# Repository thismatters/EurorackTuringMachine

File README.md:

# Turing Machine

The Turing Machine is a hugely popular module which produces random sequences of configurable length which can be held constant, or allowed to change slowly over time. Think of it like a sample-hold for sequences.

The circuit here is based on the [Music Thing Modular Turing Machine](https://github.com/TomWhitwell/TuringMachine) with some minor tweaks. The changes I've made are thus:
* Added polarity protection so that a backward power header doesn't fry anything (twin series schotty diodes: BAT54SL),
* Full surface mount design on a single PCB,
* Simpler input power filtering,
* Expanded length choices to include 7, 9, 11, and 13 (in addition to the default 2, 3, 4, 5, 6, 8, 12, and 16).
* Schmitt trigger with hysteresis on clock input to handle input signals which aren't perfectly smooth (alleviating the tendancy of the Music Thing Modular circuit to double-clock)

This module should be a drop-in replacement for the Musing Thing Modular version with the same width and same basic panel layout. I've altered it somewhat to fit with the aesthetic and practices of my DIY build, however the pinouts for expansion modules adhere exactly to the original. This repo inherits the same license as the original Turing Machine: [CC-BY-SA](https://creativecommons.org/licenses/by-sa/3.0/)

The KiCAD project here uses the library/footprints [found in my companion repo](https://github.com/thismatters/EurorackKiCAD).

Note resistors R1 and R2 have been removed. You will not find them in the schematic or BOM.

## Width

10hp

## Inputs

Jacks:
- Clock (required input) -- Max clock rate: 1300Hz; higher frequencies will cause bit smearing.
- CV for setting "Change" rate

Knobs:
- Change rate
- Sequence length (12 position switch)
- Scale

Write switch for setting the current bit high or low.

## Outputs

Jacks:
- CV output of of sequence
- Whitenoise
- Pulse whenever the current bit is high

LEDs:
- 8x for the current binary representation of the output tone
- 1x for the pulse
- 1x for the clock input

## Vendors

There are part numbers in the [BOM](turing-machine.csv) for many of the parts (not for basic passives though) at the following vendors:

* [Mouser](https://www.mouser.com): Needs no introduction. Get your ICs from here (or [digikey](https://www.digikey.com)).
* [Tayda Electronics](https://www.taydaelectronics.com/): Good supplier for passive components; audio jacks, and potentiometers. Their audio jacks are slightly smaller than the thonkiconn from thonk.
* [Love My Switches](https://lovemyswitches.com/): Has [really good knobs](https://lovemyswitches.com/anodized-aluminum-knob-the-lo-fi-1-4-smooth-shaft-12-5mm-od/) to go on those potentiometers!
* [OSHPark](https://oshpark.com/): Fast and (relatively) cheap PCB manufacturer. ~[V1 board works great!](https://oshpark.com/shared_projects/wF94N3Eb)~ There is a problem with the randomness and change circuitry. Needs a new version.

## Changelog

### V1

* [x] Fixed pinout for DAC0800 which is different for SOIC than PDIP
* [x] Write switch rotated 180deg
* [x] Filters between shift registers removed (max clock rate confirmed at around 1330Hz (E6))
* [x] Schmitt trigger supplements op-amp in gate input stage
* [x] Flipped trimmer and added hole to front panel so that trimming can happen _in-situ_, added note to PCB about how the trimmer should be oriented.

### V1a

* [x] Corrected C12 to have value of 1nF
* [x] Added test points for:
  * LOOP_CTRL'
  * RAND'
* [x] Investigated noise interference
  * When several LEDs are lit the noise level drops dramatically
  * clipping the LEDS from the prototype PCB alleviated the problem.
  * It seems produent to run the LEDS from the buffer outputs (which drive the expanders), and to drive the buffers from an isolated power circuit.
* [x] tested the V1 circuit driving LEDs from expander to see if secondary power circuit is necessary
  * it is. Driving the LEDs via the buffer still brings the +12V rail from 11.45V to 11.15V
* [x] Tested if ferrite bead in place of 10ohm resistor for power conditioning corrects noise interference issue (seems to work fine)
* [x] Updated power circuit to use ferrite bead (81-BLM21SP700BH1D) instead of resistor to more closely match original design

#### V1 -> V1a refit
* Change capacitor C12 value to 1nF.
* Use ferrite bead in place of resistors R1 and R2. A suitable part with an matching footprint is available from Mouser.com: part number 81-BLM21SP700BH1D.

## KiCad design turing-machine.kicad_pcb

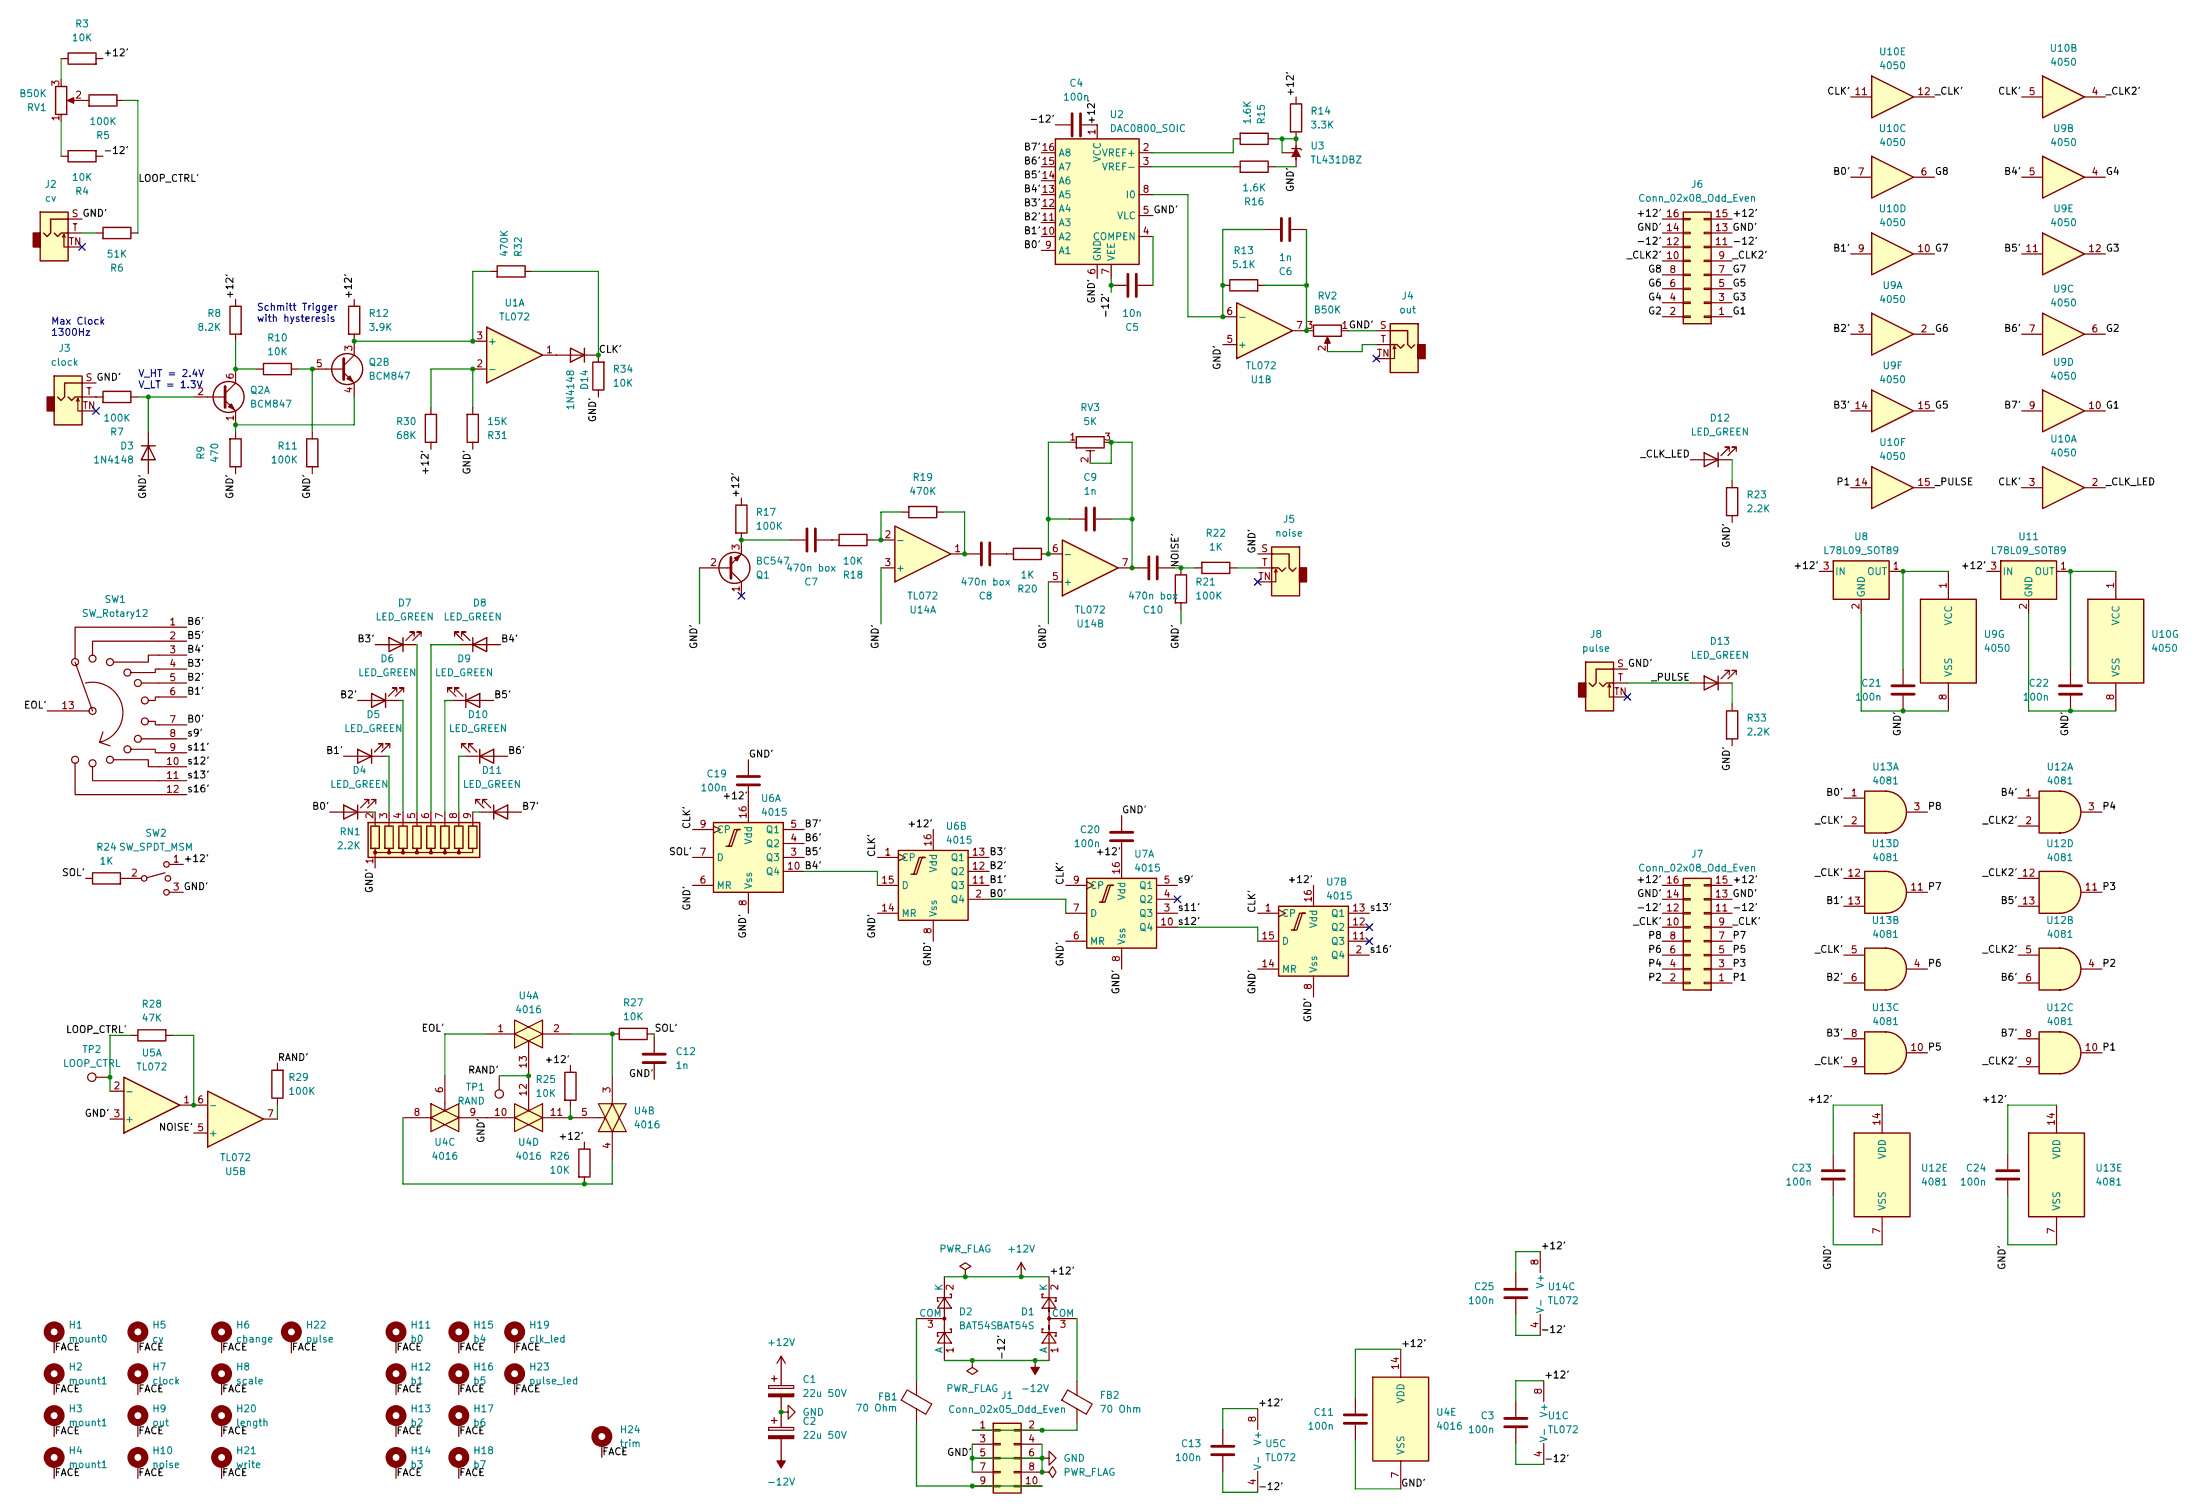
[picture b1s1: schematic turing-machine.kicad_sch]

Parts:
C1, C2: 22u 50V; CP_Radial_D5.0mm_P2.50mm
C3, C4, C11, C13, C19, C20, C21, C22, C23, C24, C25: 100n; C_0805_2012Metric
C5: 10n; C_0805_2012Metric
C6, C9, C12: 1n; C_0805_2012Metric
C7, C8, C10: 470n box; C_Rect_L7.2mm_W4.5mm_P5.00mm_FKS2_FKP2_MKS2_MKP2
D1, D2: BAT54S; SOT-23; PartNum 863-BAT54SLT1G
D3, D14: 1N4148; D_SOD-323_HandSoldering
D4, D5, D6, D7, D8, D9, D10, D11, D12, D13: LED_GREEN; LED_D3.0mm
FB1, FB2: 70 Ohm; L_0805_2012Metric; PartNum 81-BLM21SP700BH1D
H1: mount0; Mech-MountingHole
H2, H3, H4: mount1; Mech-MountingHole
H5: cv; Mech-AudioJack-Hole-Input-CV
H6: change; Mech-Potentiometer-Hole_level_180deg
H7: clock; Mech-AudioJack-Hole-Input-Clock
H8: scale; Mech-Potentiometer-Hole_level
H9: out; Mech-AudioJack-Hole-Output-CV
H10: noise; Mech-AudioJack-Hole-Output
H11: b0; Mech-LED-Hole-3mm
H12: b1; Mech-LED-Hole-3mm
H13: b2; Mech-LED-Hole-3mm
H14: b3; Mech-LED-Hole-3mm
H15: b4; Mech-LED-Hole-3mm
H16: b5; Mech-LED-Hole-3mm
H17: b6; Mech-LED-Hole-3mm
H18: b7; Mech-LED-Hole-3mm
H19: clk_led; Mech-LED-Hole-3mm
H20: length; Mech-MRK-Hole
H21: write; Mech-1M_Switch-Hole
H22: pulse; Mech-AudioJack-Hole-Output-Gate
H23: pulse_led; Mech-LED-Hole-3mm
H24: trim; Mech-LED-Hole-3mm
J1: Conn_02x05_Odd_Even; PinHeader_2x05_P2.54mm_Vertical; PartNum A-2939
J2: cv; AudioJack2_Tayda_A-2566; PartNum A-2566
J3: clock; AudioJack2_Tayda_A-2566; PartNum A-2566
J4: out; AudioJack2_Tayda_A-2566; PartNum A-2566
J5: noise; AudioJack2_Tayda_A-2566; PartNum A-2566
J6, J7: Conn_02x08_Odd_Even; PinHeader_2x08_P2.54mm_Vertical; PartNum A-2956
J8: pulse; AudioJack2_Tayda_A-2566; PartNum A-2566
Q1: BC547; TO-92_Inline_Wide; PartNum 637-BC547C
Q2: BCM847; TSOP-6_1.65x3.05mm_P0.95mm; PartNum 771-BCM847DS135
R3, R4, R10, R18, R25, R26, R27, R34: 10K; R_0805_2012Metric
R5, R7, R11, R17, R21, R29: 100K; R_0805_2012Metric
R6: 51K; R_0805_2012Metric
R8: 8.2K; R_0805_2012Metric
R9: 470; R_0805_2012Metric
R12: 3.9K; R_0805_2012Metric
R13: 5.1K; R_0805_2012Metric
R14: 3.3K; R_0805_2012Metric
R15, R16: 1.6K; R_0805_2012Metric
R19, R32: 470K; R_0805_2012Metric
R20, R22, R24: 1K; R_0805_2012Metric
R23, R33: 2.2K; R_0805_2012Metric
R28: 47K; R_0805_2012Metric
R30: 68K; R_0805_2012Metric
R31: 15K; R_0805_2012Metric
RN1: 2.2K; R_Array_SIP9; PartNum 652-4609X-1LF-2.2K
RV1, RV2: B50K; Potentiometer_RV16AF-41-15R1
RV3: 5K; Potentiometer_Bourns_3296W_Vertical
SW1: SW_Rotary12; Switch_Rotary_NKK_MRK_112; PartNum 633-MRK112-BA
SW2: SW_SPDT_MSM; Switch_SPDT_1M_Solder_Lug; PartNum A-6099
TP1: RAND; TestPoint_Plated_Hole_D2.0mm
TP2: LOOP_CTRL; TestPoint_Plated_Hole_D2.0mm
U1, U5, U14: TL072; SOIC-8_3.9x4.9mm_P1.27mm; PartNum 595-TL072CDR
U2: DAC0800_SOIC; SOIC-16_3.9x9.9mm_P1.27mm; PartNum 926-DAC0800LCMX/NOPB
U3: TL431DBZ; SOT-23; PartNum 595-TL431BCDBZTG4
U4: 4016; TSSOP-14_4.4x5mm_P0.65mm; PartNum 595-CD4016BPWR
U6, U7: 4015; TSSOP-16_4.4x5mm_P0.65mm; PartNum 595-CD4015BPWR
U8, U11: L78L09_SOT89; SOT-89-3; PartNum 511-L78L09ACU
U9, U10: 4050; TSSOP-16_4.4x5mm_P0.65mm; PartNum 595-CD4050BPWR
U12, U13: 4081; TSSOP-14_4.4x5mm_P0.65mm; PartNum 595-CD4081BPWR

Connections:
+12V: C1.1, C3.1, C4.2, C11.1, C13.1, C19.2, C20.2, C23.1, C24.1, C25.1, D1.2 (K), D2.2 (K), J6.15, J6.16, J7.15, J7.16, R3.2, R8.1, R12.1, R14.1, R17.1, R25.1, R26.1, R30.2, SW2.1, U1.8 (V+), U2.1 (VCC), U4.14 (VDD), U5.8 (V+), U6.16 (Vdd), U7.16 (Vdd), U8.3 (IN), U11.3 (IN), U12.14 (VDD), U13.14 (VDD), U14.8 (V+)
-12V: C2.2, C3.2, C4.1, C5.1, C13.2, C25.2, D1.1 (A), D2.1 (A), J6.11, J6.12, J7.11, J7.12, R4.2, U1.4 (V-), U2.7 (VEE), U5.4 (V-), U14.4 (V-)
/B0': D4.2 (A), SW1.7, U2.9 (A1), U6.2 (Q4), U7.7 (D), U10.7, U13.1
/B1': D5.2 (A), SW1.6, U2.10 (A2), U6.11 (Q3), U10.9, U13.13
/B2': D6.2 (A), SW1.5, U2.11 (A3), U6.12 (Q2), U9.3, U13.6
/B3': D7.2 (A), SW1.4, U2.12 (A4), U6.13 (Q1), U9.14, U13.8
/B4': D8.2 (A), SW1.3, U2.13 (A5), U6.10 (Q4), U6.15 (D), U9.5, U12.1
/B5': D9.2 (A), SW1.2, U2.14 (A6), U6.3 (Q3), U9.11, U12.13
/B6': D10.2 (A), SW1.1, U2.15 (A7), U6.4 (Q2), U9.7, U12.6
/B7': D11.2 (A), U2.16 (A8), U6.5 (Q1), U9.9, U12.8
/CLK': D14.1 (K), R32.1, R34.2, U6.1 (CP), U6.9 (CP), U7.1 (CP), U7.9 (CP), U10.3, U10.5, U10.11
/EOL': SW1.13, U4.1, U4.6
/FACE: H1.1, H2.1, H3.1, H4.1, H5.1, H6.1, H7.1, H8.1, H9.1, H10.1, H11.1, H12.1, H13.1, H14.1, H15.1, H16.1, H17.1, H18.1, H19.1, H20.1, H21.1, H22.1, H23.1, H24.1
/G1: J6.1, U9.10
/G2: J6.2, U9.6
/G3: J6.3, U9.12
/G4: J6.4, U9.4
/G5: J6.5, U9.15
/G6: J6.6, U9.2
/G7: J6.7, U10.10
/G8: J6.8, U10.6
/LOOP_CTRL': R5.1, R6.1, R28.1, TP2.1, U5.2 (-)
/NOISE': C10.2, R21.1, R22.2, U5.5 (+)
/P1: J7.1, U10.14, U12.10
/P2: J7.2, U12.4
/P3: J7.3, U12.11
/P4: J7.4, U12.3
/P5: J7.5, U13.10
/P6: J7.6, U13.4
/P7: J7.7, U13.11
/P8: J7.8, U13.3
/RAND': R29.2, TP1.1, U4.12, U4.13
/SOL': C12.1, R24.1, R27.2, U6.7 (D)
/_CLK2': J6.9, J6.10, U10.4, U12.2, U12.5, U12.9, U12.12
/_CLK': J7.9, J7.10, U10.12, U13.2, U13.5, U13.9, U13.12
/_CLK_LED: D12.2 (A), U10.2
/_PULSE: D13.2 (A), J8.T, U10.15
/s9': SW1.8, U7.5 (Q1)
/s11': SW1.9, U7.3 (Q3)
/s12': SW1.10, U7.10 (Q4), U7.15 (D)
/s13': SW1.11, U7.13 (Q1)
/s16': SW1.12, U7.2 (Q4)
GND: C1.2, C2.1, C11.2, C12.2, C19.1, C20.1, C21.2, C22.2, C23.2, C24.2, D3.2 (A), J1.3, J1.4, J1.5, J1.6, J1.7, J1.8, J2.S, J3.S, J4.S, J5.S, J6.13, J6.14, J7.13, J7.14, J8.S, Q1.2 (B), R9.1, R11.2, R16.1, R21.2, R23.2, R31.1, R33.2, R34.1, RN1.1 (common), RV2.1, SW2.3, U1.5 (+), U2.5 (VLC), U2.6 (GND), U3.3 (A), U4.7 (VSS), U4.9, U4.10, U5.3 (+), U6.6 (MR), U6.8 (Vss), U6.14 (MR), U7.6 (MR), U7.8 (Vss), U7.14 (MR), U8.2 (GND), U9.8 (VSS), U10.8 (VSS), U11.2 (GND), U12.7 (VSS), U13.7 (VSS), U14.3 (+), U14.5 (+)
unnamed: C6.2, R13.2, RV2.3, U1.7
unnamed: C7.2, R18.2
unnamed: C8.1, R19.1, U14.1
unnamed: C8.2, R20.2
unnamed: C9.2, C10.1, RV3.2, RV3.3, U14.7
unnamed: D1.3 (COM), FB2.1
unnamed: D2.3 (COM), FB1.1
unnamed: D3.1 (K), Q2.2 (B1), R7.1
unnamed: D4.1 (K), RN1.2 (R1)
unnamed: D5.1 (K), RN1.3 (R2)
unnamed: D6.1 (K), RN1.4 (R3)
unnamed: D7.1 (K), RN1.5 (R4)
unnamed: D8.1 (K), RN1.6 (R5)
unnamed: D9.1 (K), RN1.7 (R6)
unnamed: D10.1 (K), RN1.8 (R7)
unnamed: D11.1 (K), RN1.9 (R8)
unnamed: D12.1 (K), R23.1
unnamed: D13.1 (K), R33.1
unnamed: D14.2 (A), U1.1
unnamed: FB2.2, J1.1, J1.2
unnamed: FB1.2, J1.9, J1.10
unnamed: J2.T, R6.2
unnamed: J3.T, R7.2
unnamed: J4.T, RV2.2
unnamed: J5.T, R22.1
unnamed: C7.1, Q1.3 (E), R17.2
unnamed: Q2.6 (C1), R8.2, R10.1
unnamed: Q2.1 (E1), Q2.4 (E2), R9.2
unnamed: Q2.5 (B2), R10.2, R11.1
unnamed: Q2.3 (C2), R12.2, R32.2, U1.3 (+)
unnamed: R3.1, RV1.3
unnamed: R4.1, RV1.1
unnamed: R5.2, RV1.2
unnamed: R24.2, SW2.2
unnamed: R25.2, U4.5, U4.11
unnamed: R26.2, U4.4, U4.8
unnamed: R27.1, U4.2, U4.3
unnamed: R29.1, U5.7
unnamed: R30.1, R31.2, U1.2 (-)
unnamed: C6.1, R13.1, U1.6 (-), U2.8 (I0)
unnamed: C5.2, U2.4 (COMPEN)
unnamed: R15.2, U2.2 (VREF+)
unnamed: R16.2, U2.3 (VREF-)
unnamed: R14.2, R15.1, U3.1 (K), U3.2 (REF)
unnamed: R28.2, U5.1, U5.6 (-)
unnamed: C21.1, U8.1 (OUT), U9.1 (VCC)
unnamed: C22.1, U10.1 (VCC), U11.1 (OUT)
unnamed: R18.1, R19.2, U14.2 (-)
unnamed: C9.1, R20.1, RV3.1, U14.6 (-)

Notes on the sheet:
Schmitt Trigger with hysteresis
Max Clock 1300Hz
V_HT = 2.4V V_LT = 1.3V

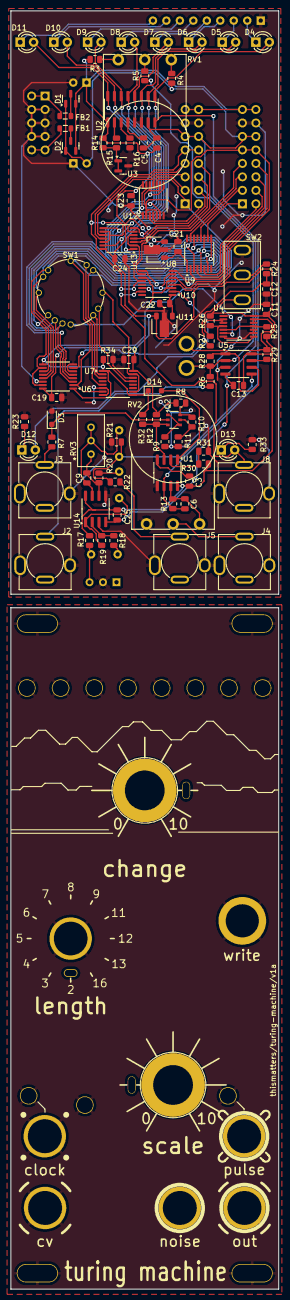
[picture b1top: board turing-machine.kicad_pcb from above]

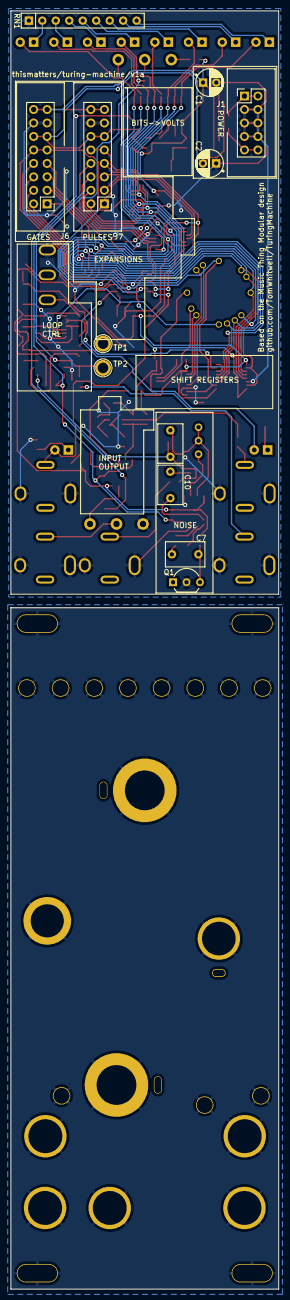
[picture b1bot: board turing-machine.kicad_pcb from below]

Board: 2 copper layers, 50.5 x 241.0 mm, 124 parts (12 on the bottom side), 92 nets.

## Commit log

2025-01-01 PCB layout complete
2025-01-01 fix: getting all parts sorted out
2025-01-05 fix: available parts only
2025-01-23 ready for v0 manu
2025-04-08 ready for v1 manu
2025-04-08 now with updated bom
2025-04-15 v1 working
2025-05-09 issue found
2026-01-01 adding results from troubleshooting
2026-01-07 v1a board ready, refit of v1 board available
